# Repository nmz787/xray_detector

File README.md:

# xray_detector
a work-in-progress x-ray detector

the last PCB I ordered is here
https://oshpark.com/shared_projects/aC3ajOJX

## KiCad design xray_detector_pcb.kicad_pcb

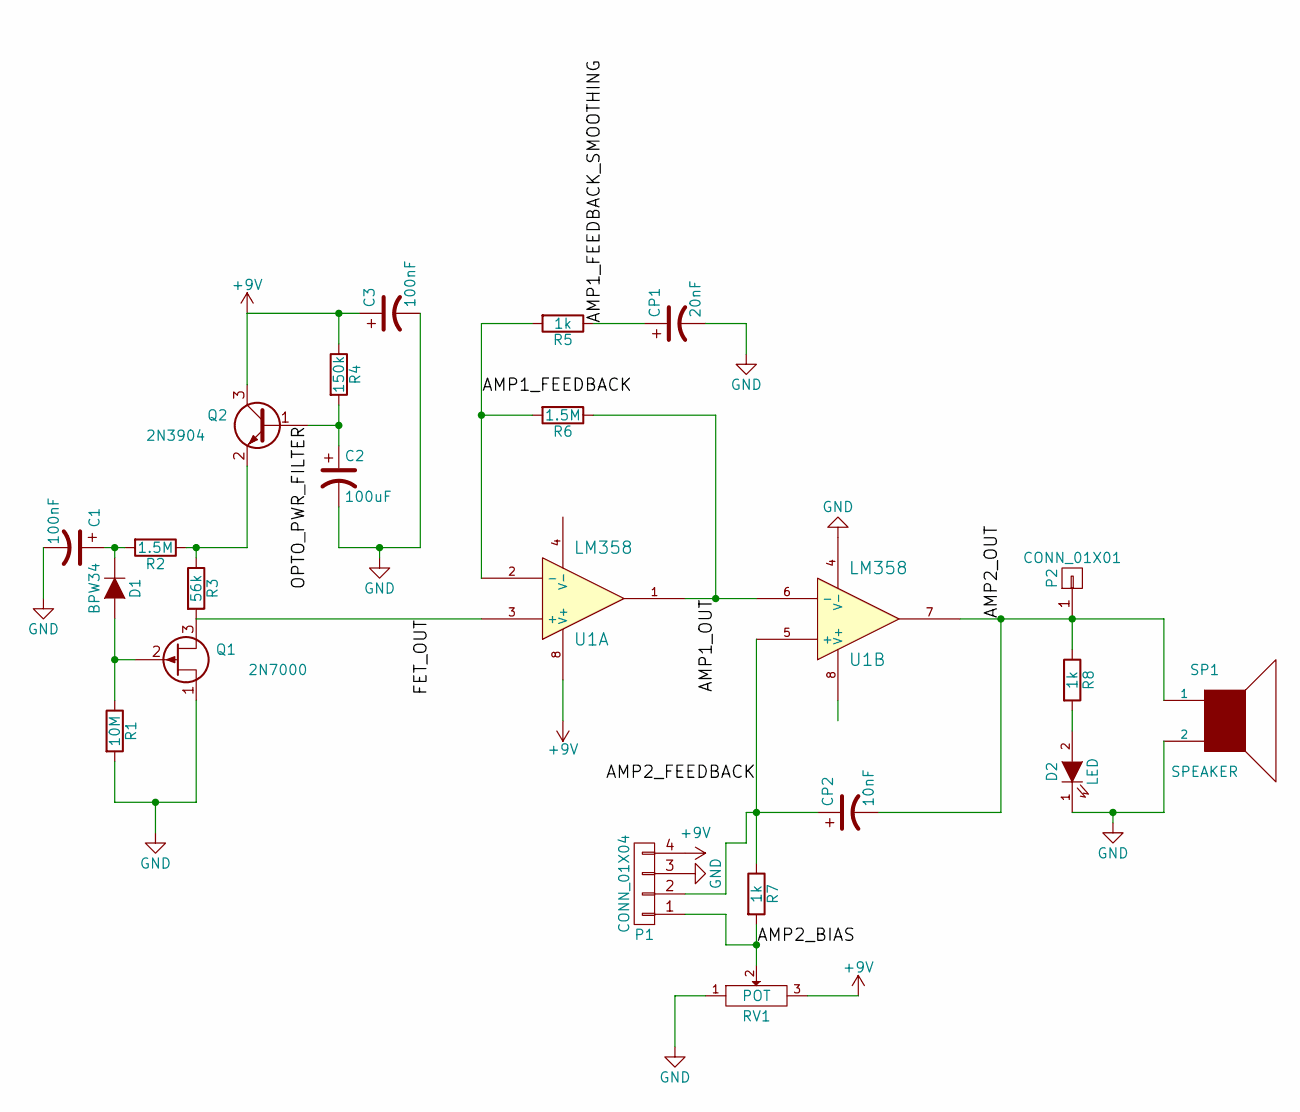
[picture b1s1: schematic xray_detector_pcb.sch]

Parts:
C1, C3: 100nF; C_0603_HandSoldering
C2: 100uF; c_elec_8x10
CP1: 20nF; C_0805_HandSoldering
CP2: 10nF; C_0603_HandSoldering
D1: BPW34; BPW34SMD-onpad-via
D2: LED; LED-5MM
P1: CONN_01X04; Pin_Header_Straight_1x04
P2: CONN_01X01; Pin_Header_Straight_1x01
Q1: 2N7000; 2SK3018
Q2: 2N3904; SOT-23_Handsoldering
R1: 10M; R_1206_HandSoldering
R2, R6: 1.5M; R_1206_HandSoldering
R3: 56k; R_1206_HandSoldering
R4: 150k; R_1206_HandSoldering
R5, R7, R8: 1k; R_1206_HandSoldering
RV1: POT; Potentiometer_VishaySpectrol-Econtrim-Type36k
SP1: SPEAKER; BUZZER
U1: LM358; SSOP-8

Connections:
+9V: C3.1, P1.4, Q2.3 (C), R4.1, RV1.3, U1.8 (V+)
/AMP1_FEEDBACK: R5.2, R6.2, U1.2 (-)
/AMP1_FEEDBACK_SMOOTHING: CP1.1, R5.1
/AMP1_OUT: R6.1, U1.1, U1.6 (-)
/AMP2_BIAS: P1.1, R7.2, RV1.2
/AMP2_FEEDBACK: CP2.1, P1.2, R7.1, U1.5 (+)
/AMP2_OUT: CP2.2, P2.1, R8.1, SP1.1, U1.7
/FET_OUT: Q1.3 (D), R3.2, U1.3 (+)
/OPTO_PWR_FILTER: C2.1, Q2.1 (B), R4.2
GND: C1.2, C2.2, C3.2, CP1.2, D2.1 (K), P1.3, Q1.1 (S), R1.2, RV1.1, SP1.2, U1.4 (V-)
unnamed: C1.1, D1.1 (K), R2.2
unnamed: D1.2 (A), Q1.2 (G), R1.1
unnamed: D2.2 (A), R8.2
unnamed: Q2.2 (E), R2.1, R3.1

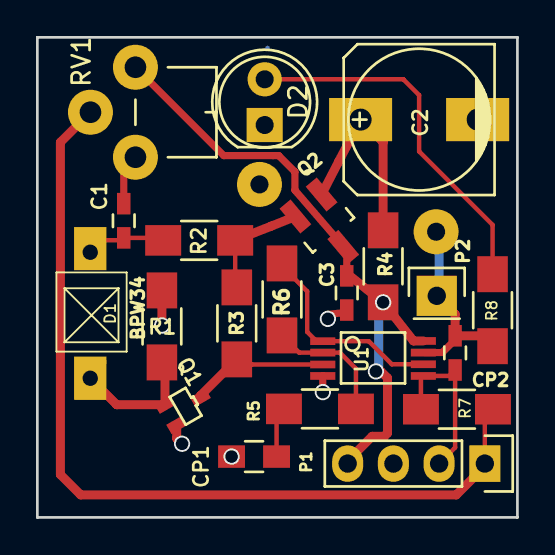
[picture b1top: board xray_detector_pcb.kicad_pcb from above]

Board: 2 copper layers, 26.7 x 26.7 mm, 22 parts (1 on the bottom side), 14 nets.

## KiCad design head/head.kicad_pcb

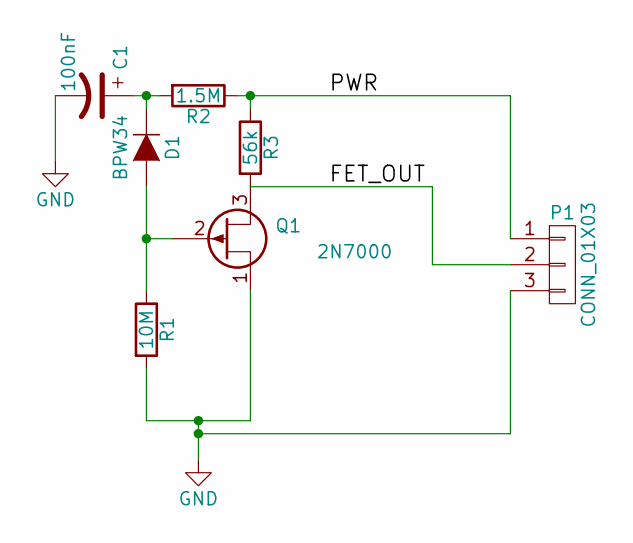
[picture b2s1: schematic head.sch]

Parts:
C1: 100nF; C_0603_HandSoldering
D1: BPW34; BPW34SMD-onpad-via
P1: CONN_01X03; SolderWirePad_3x_2mmDrill
Q1: 2N7000; 2SK3018
R1: 10M; R_1206_HandSoldering
R2: 1.5M; R_1206_HandSoldering
R3: 56k; R_1206_HandSoldering

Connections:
/FET_OUT: P1.2, Q1.3 (D), R3.2
/PWR: P1.1, R2.1, R3.1
GND: C1.2, P1.3, Q1.1 (S), R1.2
unnamed: C1.1, D1.1 (K), R2.2
unnamed: D1.2 (A), Q1.2 (G), R1.1

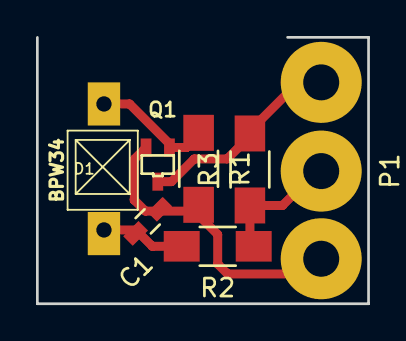
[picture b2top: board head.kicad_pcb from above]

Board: 2 copper layers, 18.4 x 14.8 mm, 7 parts (0 on the bottom side), 5 nets.

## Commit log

2017-10-19 two revs of the board, but I haven't really debugged, and didn't have a good test plan other than optical light source
2017-10-19 updated with oshpark link to last PCB I ordered
